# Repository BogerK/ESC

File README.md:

# ESC-board-for-BLDC-motor
Electronic speed controller board based on Arduino nano.
Power source - 4x Lithium-Ion batteries (4 x 3.7 V, 30A)
Application: Dji Snail motor.

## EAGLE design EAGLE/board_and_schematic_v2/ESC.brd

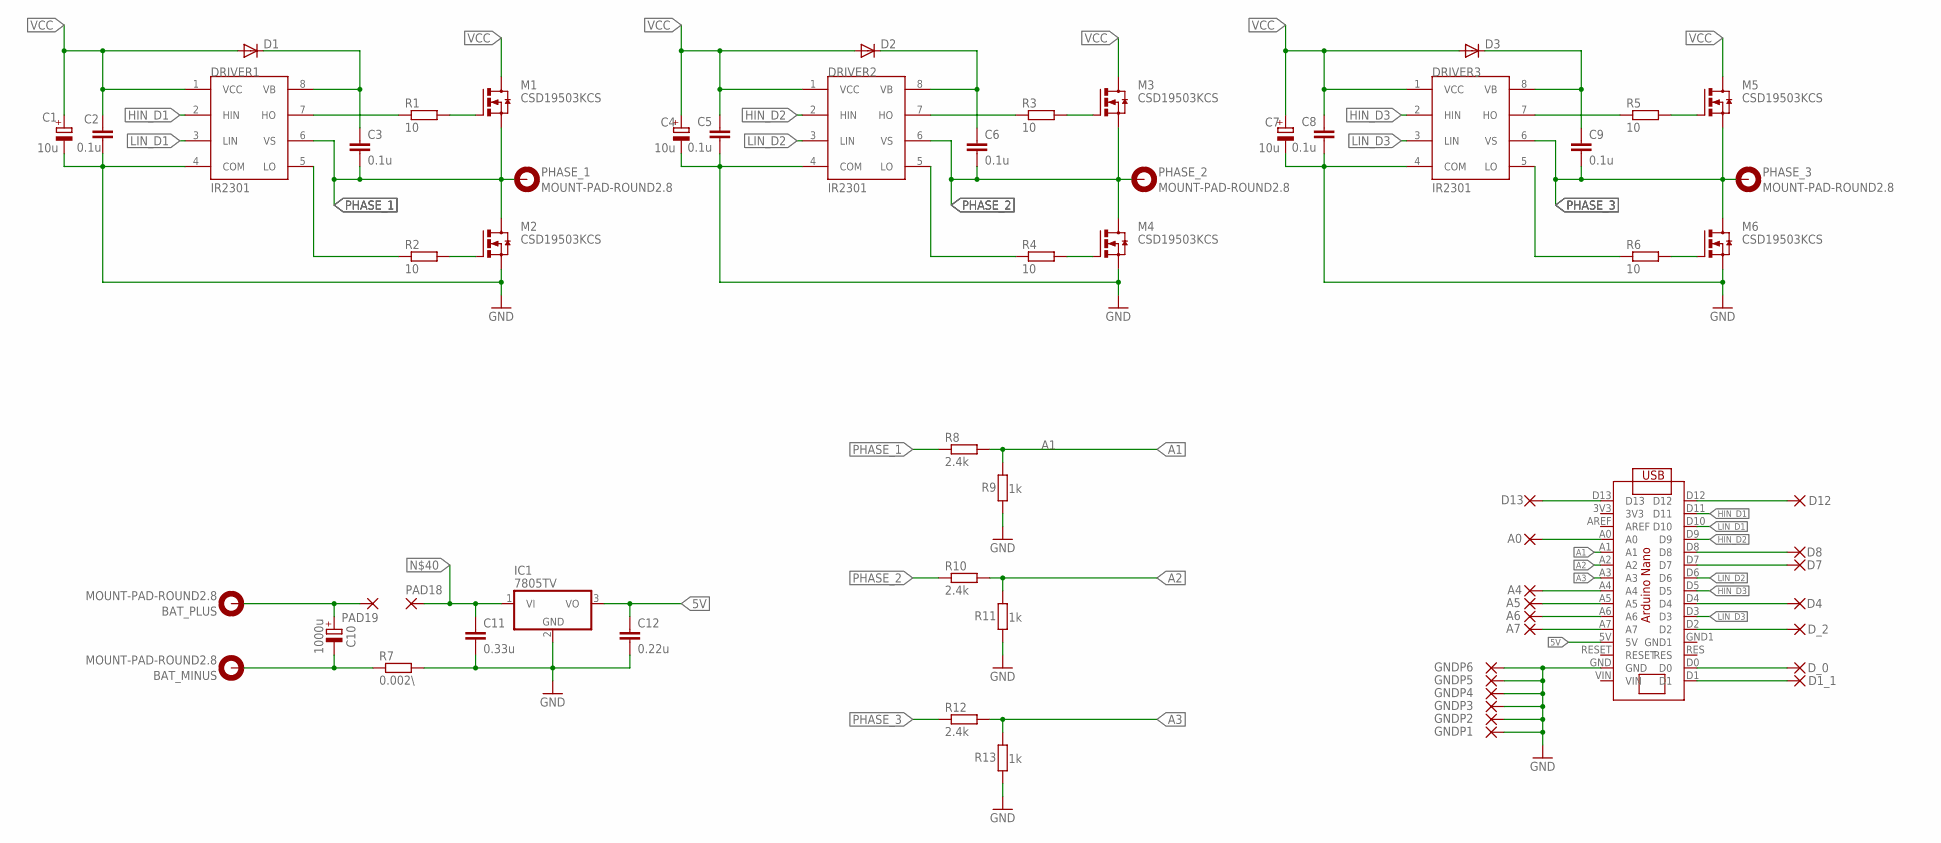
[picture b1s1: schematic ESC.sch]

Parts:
A0, A4, A5, A6, A7: 3,81/1,4
BAT_MINUS: MOUNT-PAD-ROUND2.8; 2,8-PAD
BAT_PLUS: MOUNT-PAD-ROUND2.8; 2,8-PAD
C1, C4, C7: 10u; PANASONIC_C
C2, C3, C5, C6, C8, C9: 0.1u; C1206
C10: 1000u; E7,5-16
C11: 0.33u; C1206
C12: 0.22u; C1206
D1, D2, D3: DIODE-DO41-10; DO41-10
D1_1, D4, D7, D8, D12, D13: 3,81/1,4
DRIVER1, DRIVER2, DRIVER3: IR2301; DIL08
D_0, D_2: 3,81/1,4
GNDP1, GNDP2, GNDP3, GNDP4, GNDP5, GNDP6: 3,81/1,4
IC1: 7805TV; TO220V
M1, M2, M3, M4, M5, M6: CSD19503KCS; TO220BV
PAD18, PAD19: 3,81/1,4
PHASE_1, PHASE_2, PHASE_3: MOUNT-PAD-ROUND2.8; 2,8-PAD
R1, R2, R3, R4, R5, R6: 10; R1206
R7: 0.002\; R2512
R8, R10, R12: 2.4k; R1206
R9, R11, R13: 1k; R1206
U$7: ARDUINO-NANO

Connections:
5V: C12.1, IC1.3 (VO), U$7.5V
A1: R8.2, R9.2, U$7.A1
A2: R10.2, R11.2, U$7.A2
A3: R12.2, R13.2, U$7.A3
BAT_MINUS: BAT_MINUS.B2,8, C10.-, R7.1
D22: D_2.1, U$7.D2
GND: C1.-, C2.2, C4.-, C5.2, C7.-, C8.2, C11.2, C12.2, DRIVER1.4 (COM), DRIVER2.4 (COM), DRIVER3.4 (COM), GNDP1.1, GNDP2.1, GNDP3.1, GNDP4.1, GNDP5.1, GNDP6.1, IC1.2 (GND), M2.S, M4.S, M6.S, R7.2, R9.1, R11.1, R13.1, U$7.GND
HIN_D1: DRIVER1.2 (HIN), U$7.D11
HIN_D2: DRIVER2.2 (HIN), U$7.D9
HIN_D3: DRIVER3.2 (HIN), U$7.D5
LIN_D1: DRIVER1.3 (LIN), U$7.D10
LIN_D2: DRIVER2.3 (LIN), U$7.D6
LIN_D3: DRIVER3.3 (LIN), U$7.D3
unnamed: DRIVER2.7 (HO), R3.1
unnamed: DRIVER2.5 (LO), R4.1
unnamed: M3.G, R3.2
unnamed: D13.1, U$7.D13
unnamed: DRIVER3.7 (HO), R5.1
unnamed: DRIVER3.5 (LO), R6.1
unnamed: A0.1, U$7.A0
unnamed: A4.1, U$7.A4
unnamed: A5.1, U$7.A5
unnamed: A6.1, U$7.A6
unnamed: A7.1, U$7.A7
unnamed: D4.1, U$7.D4
unnamed: DRIVER1.7 (HO), R1.1
unnamed: D7.1, U$7.D7
unnamed: D8.1, U$7.D8
unnamed: DRIVER1.5 (LO), R2.1
unnamed: M4.G, R4.2
unnamed: M5.G, R5.2
unnamed: D12.1, U$7.D12
unnamed: M6.G, R6.2
unnamed: D_0.1, U$7.D0
unnamed: D1_1.1, U$7.D1
unnamed: M1.G, R1.2
unnamed: M2.G, R2.2
unnamed: C11.1, IC1.1 (VI), PAD18.1
PHASE_1: C3.2, DRIVER1.6 (VS), M1.S, M2.D, PHASE_1.B2,8, R8.1
PHASE_2: C6.2, DRIVER2.6 (VS), M3.S, M4.D, PHASE_2.B2,8, R10.1
PHASE_3: C9.2, DRIVER3.6 (VS), M5.S, M6.D, PHASE_3.B2,8, R12.1
VB1: C3.1, D1.C, DRIVER1.8 (VB)
VB2: C6.1, D2.C, DRIVER2.8 (VB)
VB3: C9.1, D3.C, DRIVER3.8 (VB)
VCC: BAT_PLUS.B2,8, C1.+, C2.1, C4.+, C5.1, C7.+, C8.1, C10.+, D1.A, D2.A, D3.A, DRIVER1.1 (VCC), DRIVER2.1 (VCC), DRIVER3.1 (VCC), M1.D, M3.D, M5.D, PAD19.1

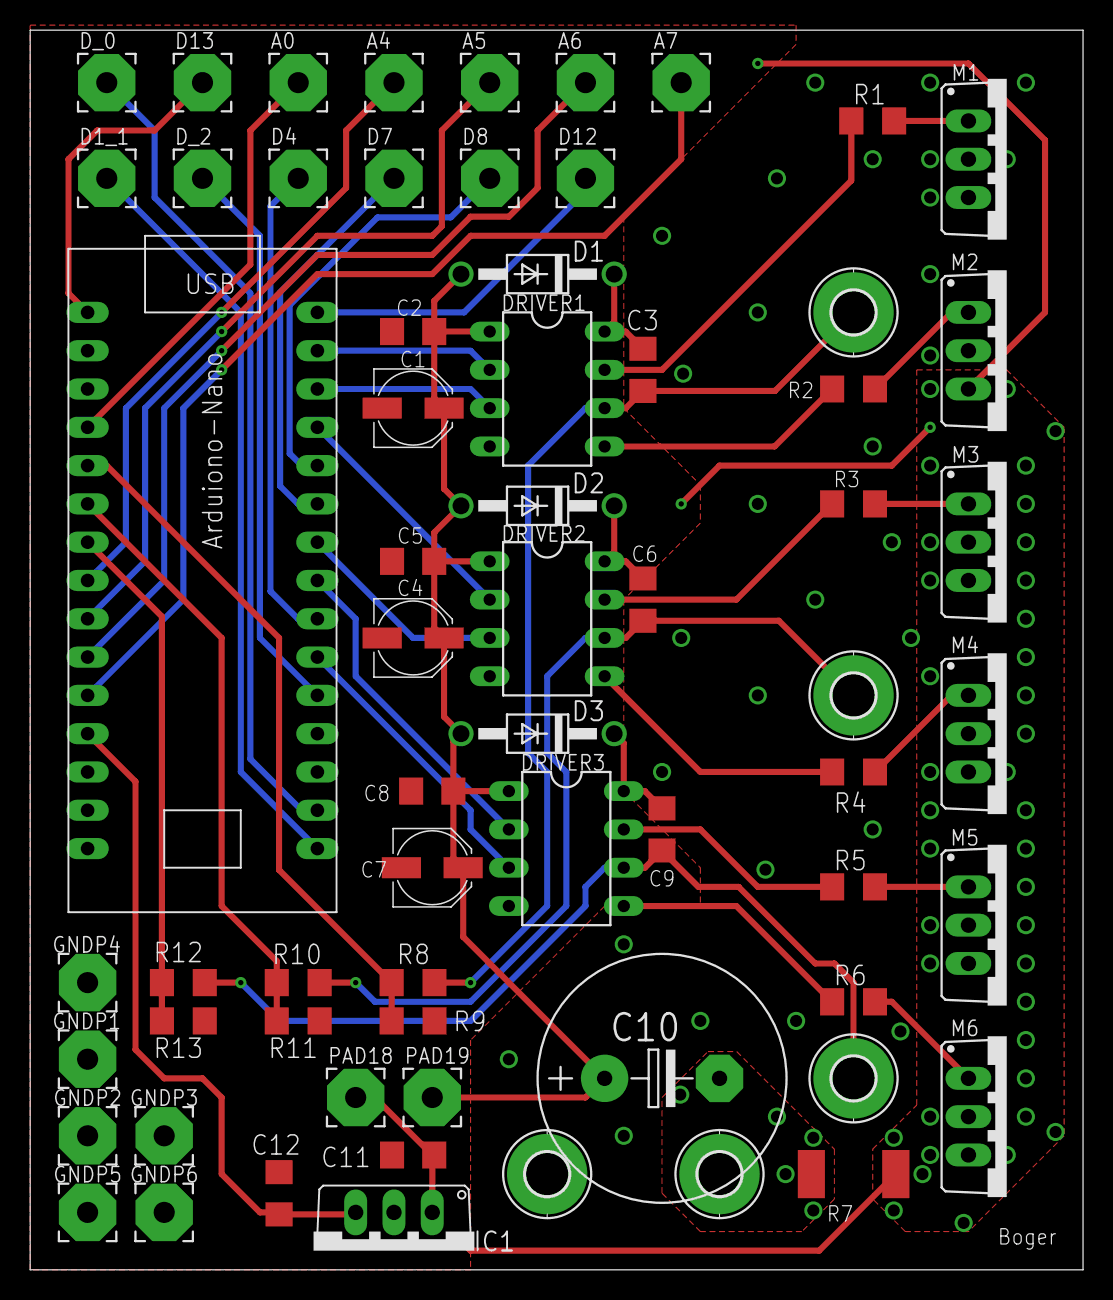
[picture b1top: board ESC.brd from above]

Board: 4 copper layers, 69.8 x 82.2 mm, 65 parts (0 on the bottom side), 45 nets.

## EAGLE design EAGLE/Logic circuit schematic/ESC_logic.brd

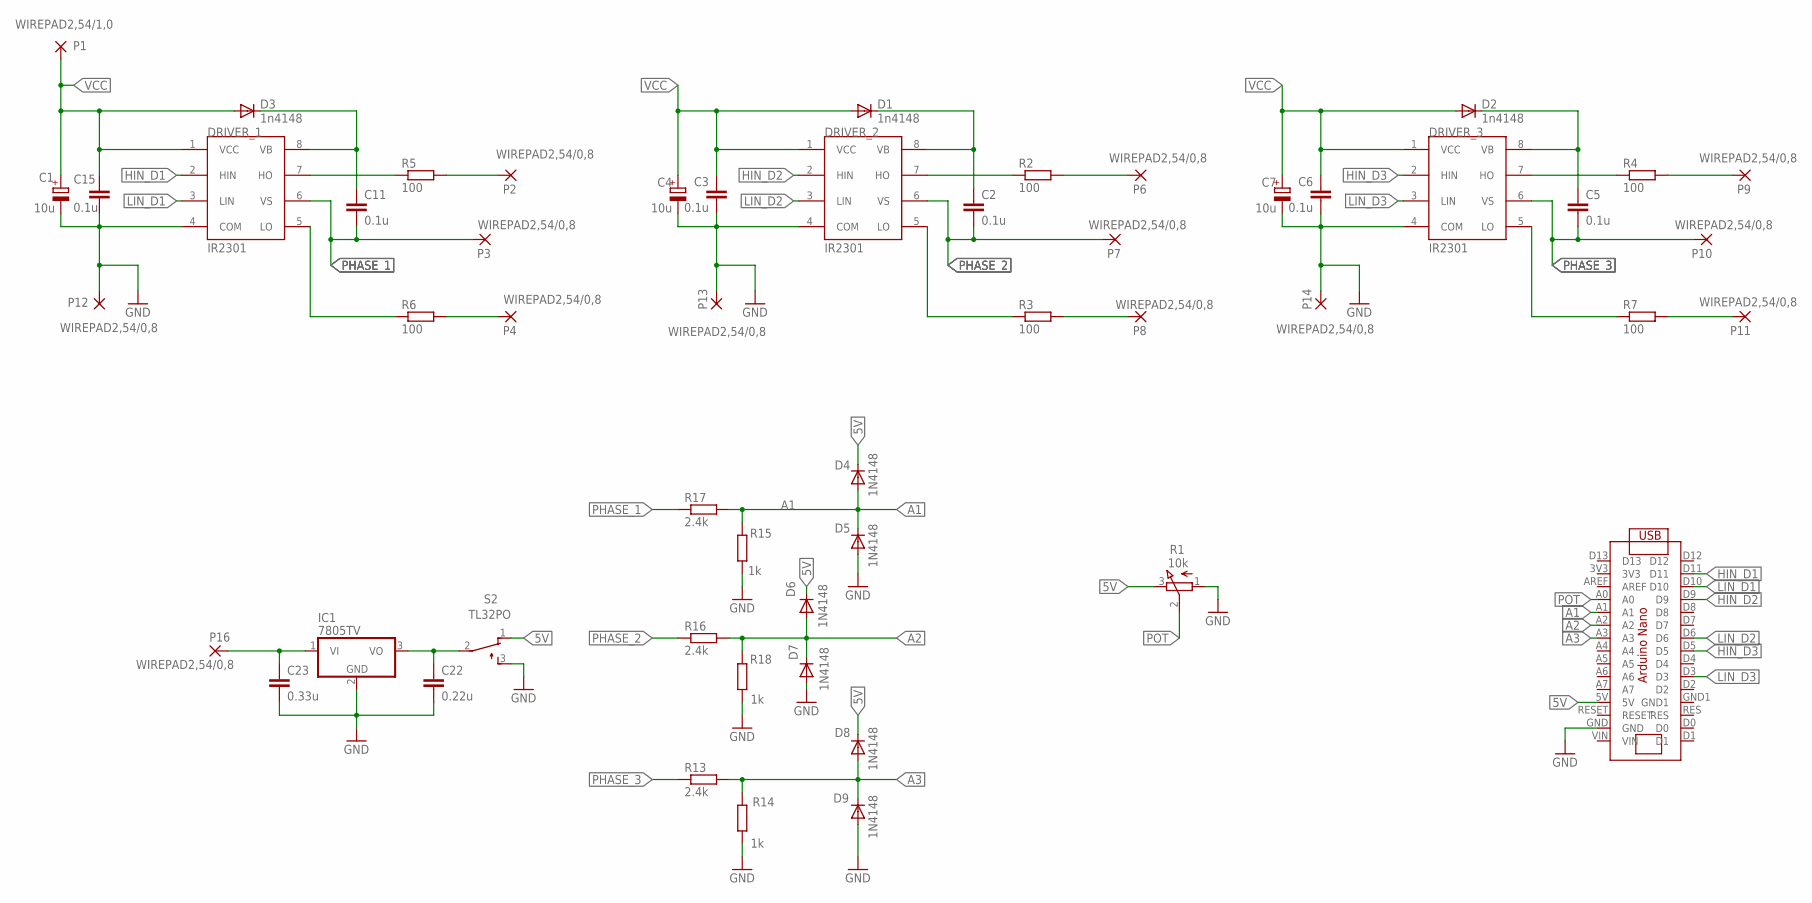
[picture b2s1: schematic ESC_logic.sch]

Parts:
C1, C4, C7: 10u; 153CLV-0605
C2, C3, C5, C6, C11, C15: 0.1u; C1206
C22: 0.22u; C1206
C23: 0.33u; C1206
D1, D2, D3: 1n4148; DO41-10
D4, D5, D6, D7, D8, D9: 1N4148; DO41-10
DRIVER_1, DRIVER_2, DRIVER_3: IR2301; DIL08
IC1: 7805TV; TO220V
P1: WIREPAD2,54/1,0; 2,54/1,0
P2, P3, P4, P6, P7, P8, P9, P10, P11, P12, P13, P14, P16: WIREPAD2,54/0,8; 2,54/0,8
R1: 10k; 3RP/1610N
R2, R3, R4, R5, R6, R7: 100; R1206
R13, R16, R17: 2.4k; R1206
R14, R15, R18: 1k; R1206
S2: TL32PO; TL3XPO
U$7: ARDUINO-NANO

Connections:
5V: D4.C, D6.C, D8.C, R1.3 (E), S2.1 (O), U$7.5V
A1: D4.A, D5.C, R15.2, R17.2, U$7.A1
A2: D6.A, D7.C, R16.2, R18.2, U$7.A2
A3: D8.A, D9.C, R13.2, R14.2, U$7.A3
GND: C1.-, C3.2, C4.-, C6.2, C7.-, C15.2, C22.2, C23.2, D5.A, D7.A, D9.A, DRIVER_1.4 (COM), DRIVER_2.4 (COM), DRIVER_3.4 (COM), IC1.2 (GND), P12.1, P13.1, P14.1, R1.1 (A), R14.1, R15.1, R18.1, S2.3 (S), U$7.GND
HIN_D1: DRIVER_1.2 (HIN), U$7.D11
HIN_D2: DRIVER_2.2 (HIN), U$7.D9
HIN_D3: DRIVER_3.2 (HIN), U$7.D5
LIN_D1: DRIVER_1.3 (LIN), U$7.D10
LIN_D2: DRIVER_2.3 (LIN), U$7.D6
LIN_D3: DRIVER_3.3 (LIN), U$7.D3
unnamed: DRIVER_2.7 (HO), R2.1
unnamed: DRIVER_2.5 (LO), R3.1
unnamed: P6.1, R2.2
unnamed: P8.1, R3.2
unnamed: DRIVER_3.7 (HO), R4.1
unnamed: DRIVER_3.5 (LO), R7.1
unnamed: P9.1, R4.2
unnamed: P11.1, R7.2
unnamed: DRIVER_1.7 (HO), R5.1
unnamed: DRIVER_1.5 (LO), R6.1
unnamed: P2.1, R5.2
unnamed: P4.1, R6.2
PHASE_1: C11.2, DRIVER_1.6 (VS), P3.1, R17.1
PHASE_2: C2.2, DRIVER_2.6 (VS), P7.1, R16.1
PHASE_3: C5.2, DRIVER_3.6 (VS), P10.1, R13.1
POT: R1.2 (S), U$7.A0
VB: C11.1, D3.C, DRIVER_1.8 (VB)
VB2: C2.1, D1.C, DRIVER_2.8 (VB)
VB3: C5.1, D2.C, DRIVER_3.8 (VB)
VCC: C1.+, C3.1, C4.+, C6.1, C7.+, C15.1, D1.A, D2.A, D3.A, DRIVER_1.1 (VCC), DRIVER_2.1 (VCC), DRIVER_3.1 (VCC), P1.1
VI: C23.1, IC1.1 (VI), P16.1
VO: C22.1, IC1.3 (VO), S2.2

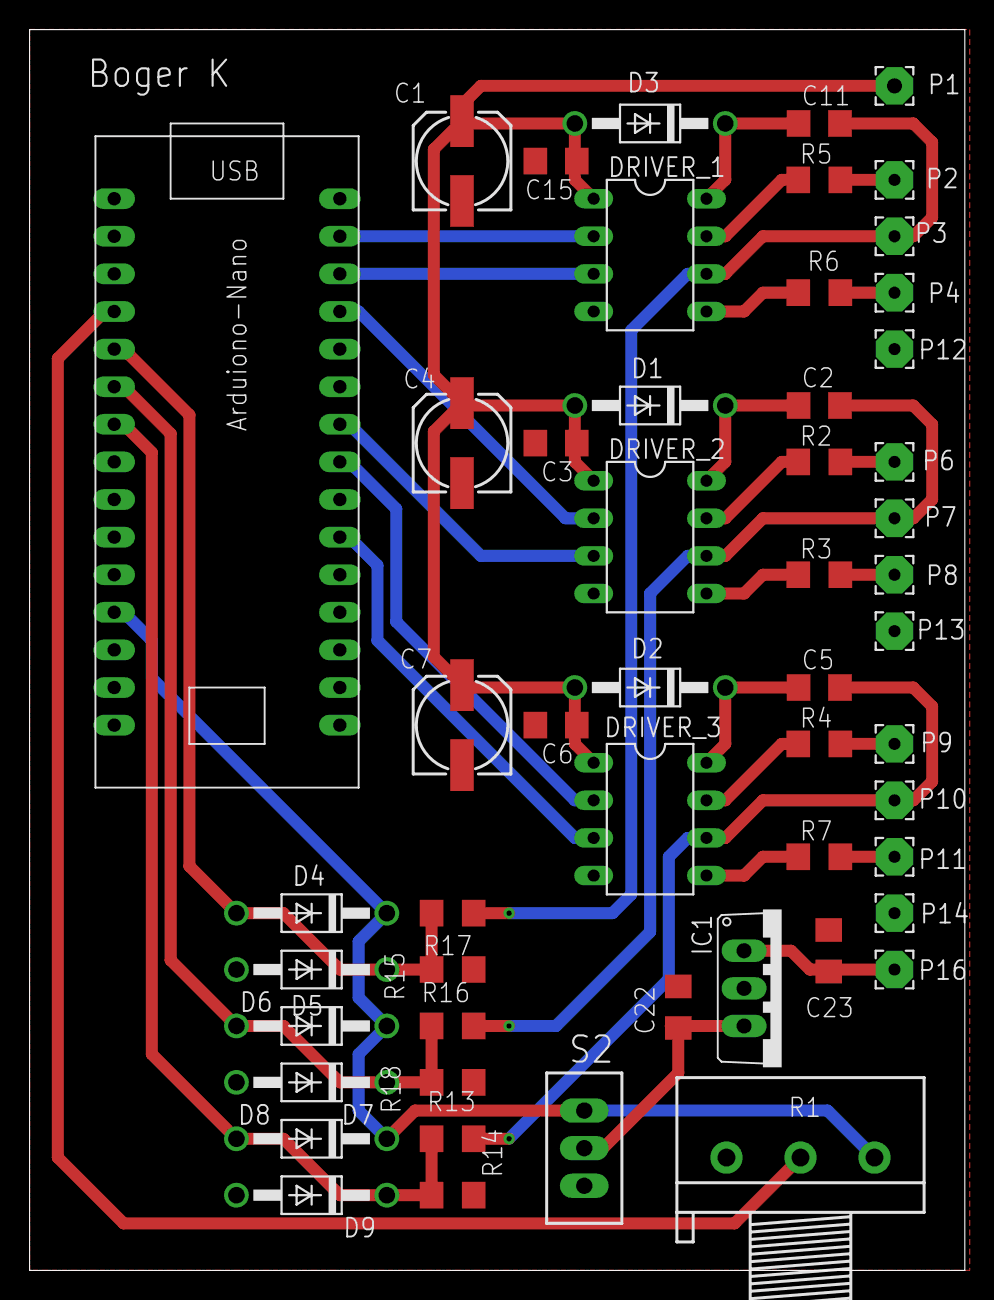
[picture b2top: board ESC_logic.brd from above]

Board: 2 copper layers, 63.2 x 83.8 mm, 53 parts (0 on the bottom side), 33 nets.

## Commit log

2019-07-15 July 15 v0.2
2019-07-15 logic circuit and general schematic seperation
2019-07-15 library fixed
2019-08-11 code update
    added code version for case when board doesn't care about back emf signal
2020-02-09 complrmrntated board
